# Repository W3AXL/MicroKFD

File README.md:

The KFDMicro (formerly known as MicroKFD) is a small, compact KFD keyfill device for P25 two-way radios.

Schematics and board layout are available in this repo. The official boards (which provide a small kickback to the original developers) can be purchased at:
https://store.w3axl.com/collections/kfd-keyloading

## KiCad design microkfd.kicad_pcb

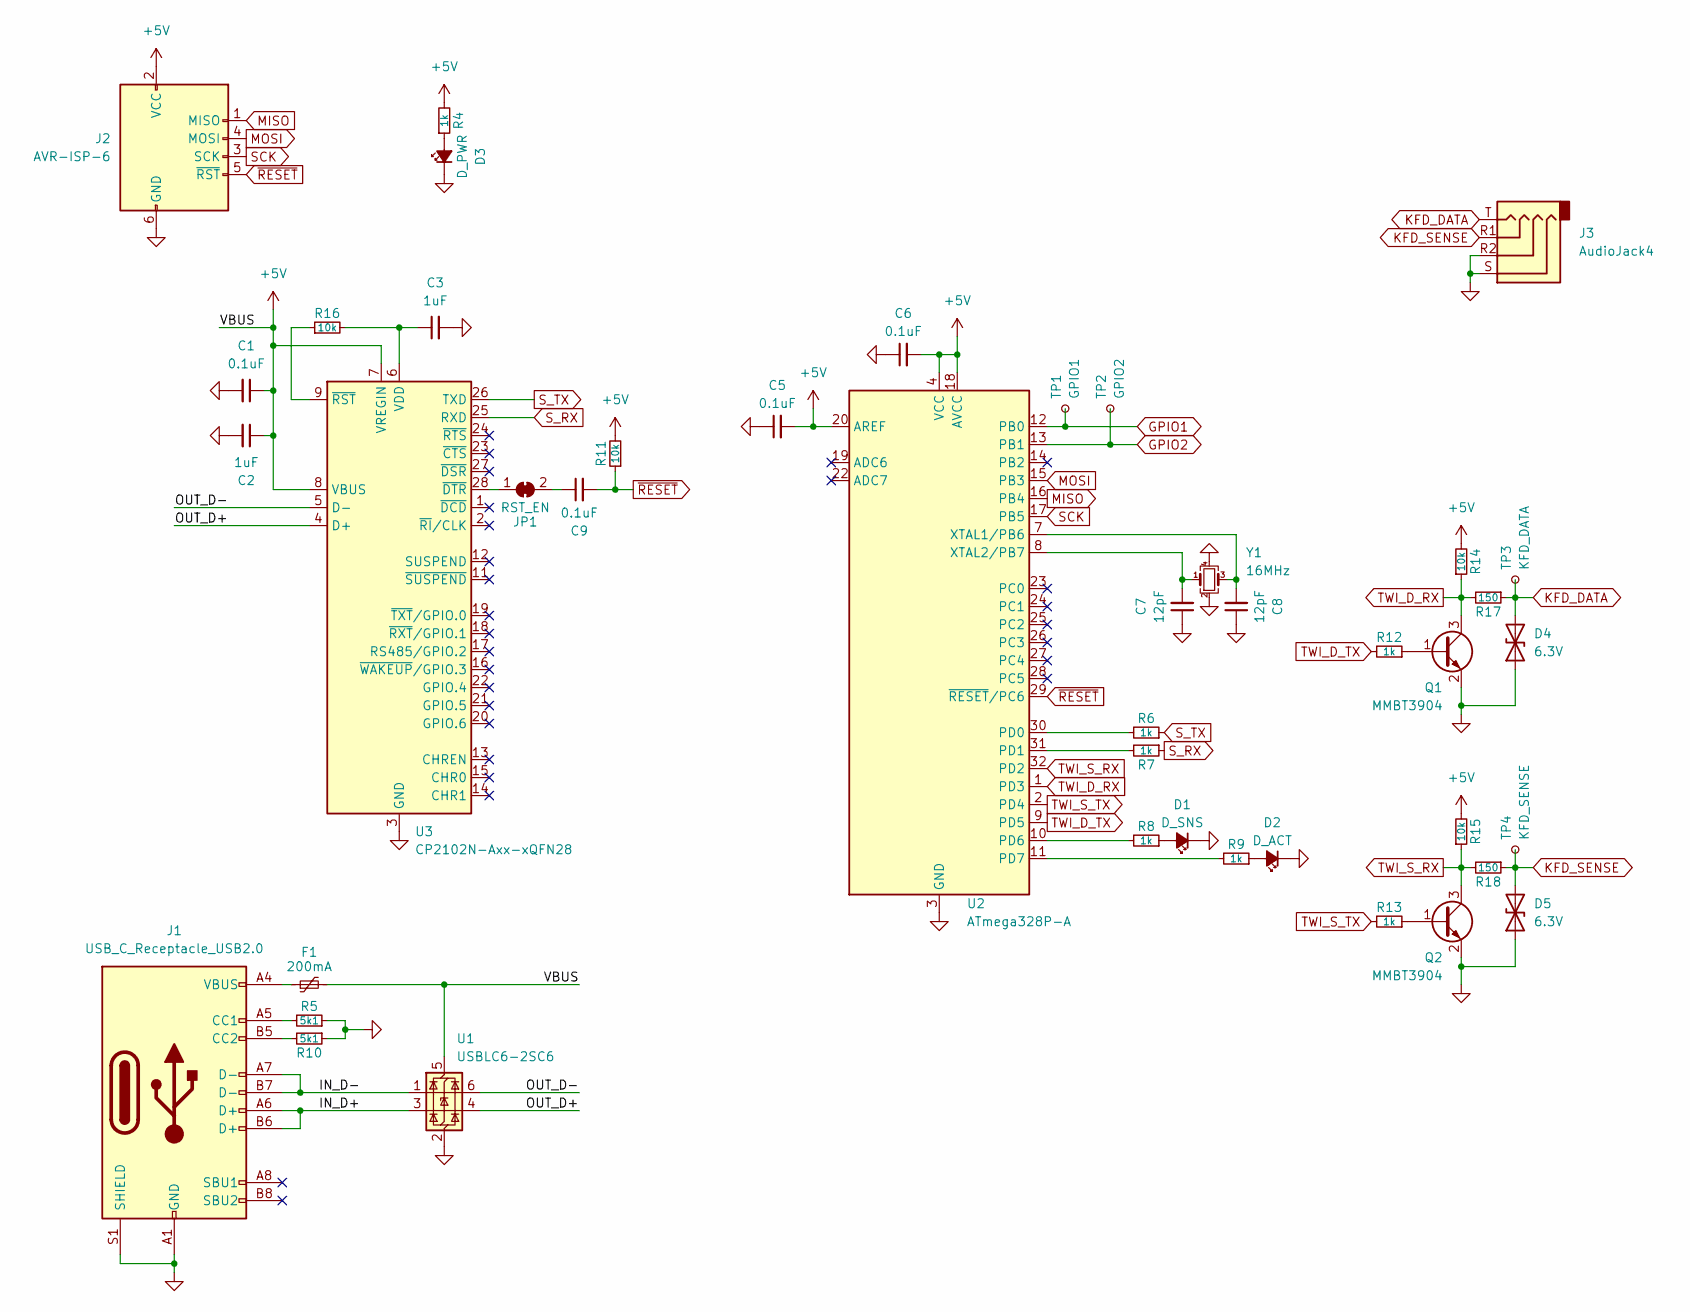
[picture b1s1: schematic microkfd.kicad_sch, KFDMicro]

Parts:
C1, C5, C6, C9: 0.1uF; C_0603_1608Metric; LCSC C28233
C2, C3: 1uF; C_0603_1608Metric; LCSC C15850
C7, C8: 12pF; C_0603_1608Metric; LCSC C1792
D1: D_SNS; LED_0805_2012Metric; LCSC C84256
D2: D_ACT; LED_0805_2012Metric; LCSC C84256
D3: D_PWR; LED_0805_2012Metric; LCSC C2297
D4, D5: 6.3V; D_0603_1608Metric; LCSC C85200
F1: 200mA; Fuse_0603_1608Metric
J1: USB_C_Receptacle_USB2.0; USB_C_Receptacle_HRO_TYPE-C-31-M-12; LCSC C2874595
J2: AVR-ISP-6; PinHeader_1x06_P2.54mm_Vertical
J3: AudioJack4; Jack_3.5mm_KoreanHropartsElec_PJ-320D-4A_Horizontal; LCSC C707216
JP1: RST_EN; SolderJumper-2_P1.3mm_Bridged_RoundedPad1.0x1.5mm
Q1, Q2: MMBT3904; SOT-23; LCSC C20526
R4, R6, R7, R8, R9, R12, R13: 1k; R_0603_1608Metric; LCSC C17513
R5, R10: 5k1; R_0603_1608Metric; LCSC C27834
R11, R14, R15, R16: 10k; R_0603_1608Metric; LCSC C17414
R17, R18: 150; R_0603_1608Metric; LCSC C17557
TP1: GPIO1; TestPoint_Pad_1.0x1.0mm
TP2: GPIO2; TestPoint_Pad_1.0x1.0mm
TP3: KFD_DATA; TestPoint_Pad_1.0x1.0mm
TP4: KFD_SENSE; TestPoint_Pad_1.0x1.0mm
U1: USBLC6-2SC6; SOT-23-6
U2: ATmega328P-A; TQFP-32_7x7mm_P0.8mm; LCSC C14877
U3: CP2102N-Axx-xQFN28; QFN-28-1EP_5x5mm_P0.5mm_EP3.35x3.35mm
Y1: 16MHz; Crystal_SMD_3225-4Pin_3.2x2.5mm; LCSC C2149025

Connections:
+5V: C1.1, C2.1, C5.2, C6.2, F1.2, J2.2 (VCC), R4.2, R11.2, R14.2, R15.2, U1.5 (VBUS), U2.4 (VCC), U2.6 (VCC), U2.18 (AVCC), U2.20 (AREF), U3.7 (VREGIN), U3.8 (VBUS)
/IN_D+: J1.A6 (D+), J1.B6 (D+), U1.3 (I/O2)
/IN_D-: J1.A7 (D-), J1.B7 (D-), U1.1 (I/O1)
/OUT_D+: U1.4 (I/O2), U3.4 (D+)
/OUT_D-: U1.6 (I/O1), U3.5 (D-)
GND: C1.2, C2.2, C3.2, C5.1, C6.1, C7.1, C8.1, D1.1 (K), D2.1 (K), D3.1 (K), D4.1 (A1), D5.1 (A1), J1.A1 (GND), J1.A12 (GND), J1.B1 (GND), J1.B12 (GND), J1.S1 (SHIELD), J2.6 (GND), J3.R2, J3.S, Q1.2 (E), Q2.2 (E), R5.1, R10.1, U1.2 (GND), U2.3 (GND), U2.5 (GND), U2.21 (GND), U3.3 (GND), U3.29 (GND), Y1.2, Y1.4
GPIO1: TP1.1, U2.12 (PB0)
GPIO2: TP2.1, U2.13 (PB1)
KFD_DATA: D4.2 (A2), J3.T, R17.1, TP3.1
KFD_SENSE: D5.2 (A2), J3.R1, R18.1, TP4.1
MISO: J2.1 (MISO), U2.16 (PB4)
MOSI: J2.4 (MOSI), U2.15 (PB3)
unnamed: D1.2 (A), R8.1
unnamed: D2.2 (A), R9.1
unnamed: D3.2 (A), R4.1
unnamed: F1.1, J1.A4 (VBUS), J1.A9 (VBUS), J1.B4 (VBUS), J1.B9 (VBUS)
unnamed: J1.A5 (CC1), R5.2
unnamed: J1.B5 (CC2), R10.2
unnamed: JP1.1 (A), U3.28 (~DTR)
unnamed: C9.1, JP1.2 (B)
unnamed: Q1.1 (B), R12.1
unnamed: Q2.1 (B), R13.1
unnamed: R6.2, U2.30 (PD0)
unnamed: R7.2, U2.31 (PD1)
unnamed: R8.2, U2.10 (PD6)
unnamed: R9.2, U2.11 (PD7)
unnamed: C8.2, U2.7 (XTAL1/PB6), Y1.3
unnamed: C7.2, U2.8 (XTAL2/PB7), Y1.1
unnamed: C3.1, R16.2, U3.6 (VDD)
unnamed: R16.1, U3.9 (~RST)
SCK: J2.3 (SCK), U2.17 (PB5)
S_RX: R7.1, U3.25 (RXD)
S_TX: R6.1, U3.26 (TXD)
TWI_D_RX: Q1.3 (C), R14.1, R17.2, U2.1 (PD3)
TWI_D_TX: R12.2, U2.9 (PD5)
TWI_S_RX: Q2.3 (C), R15.1, R18.2, U2.32 (PD2)
TWI_S_TX: R13.2, U2.2 (PD4)
~RESET: C9.2, J2.5 (~RST), R11.1, U2.29 (~RESET/PC6)

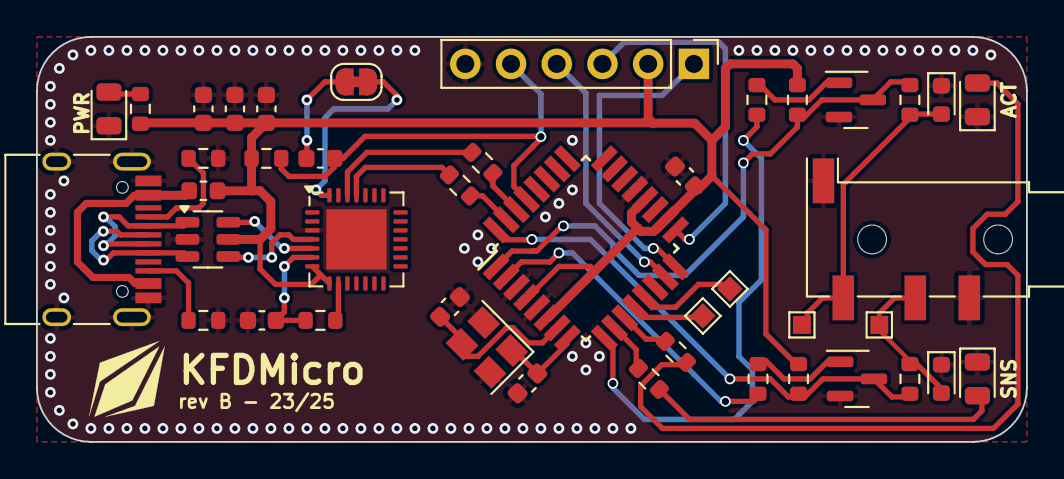
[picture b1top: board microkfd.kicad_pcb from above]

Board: 2 copper layers, 55.0 x 22.5 mm, 43 parts (0 on the bottom side), 38 nets.

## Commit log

2021-12-06 Initial project commit
2021-12-07 rev A design done
2021-12-07 added gerbers
2022-01-08 cleanups and updates
    - switched to Kicad 6.0
    - removed Kicad 5.x files
    - switched to 32u4RC due to availability
2022-01-08 finalized rev B
    switched MOSFETs due to parts availability, regenerated gerbers
2022-01-19 revC updates
    fixed missing data input line (now runs to PC2 interrupt pin)
2022-04-09 rev D: fixed pin mappings
    changed pin mappings to be closer to original KFDShield, added correct sense and data lines
2022-05-26 added logo to PCB
2022-05-26 updated gerbers for logo change
2023-01-18 revision E - atmega328p redesign
2023-05-29 finalized 328p design
2023-05-29 updated gerbers
2023-06-20 final rev F DFM updates
2023-06-20 updated DFM docs
2023-06-20 fixed pos
2023-10-02 updated to gitignore
2023-10-13 updated to revA.1
2024-10-25 dfm updates 2024
2025-06-05 rev B hardware updates
2025-06-05 fixed audio connector PN
2025-06-05 fixed audio connector model
2025-06-05 final revB updates for dev mfr run
